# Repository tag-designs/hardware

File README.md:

# Tag Designs: Hardware

Board and mechanical designs for the ultralight archival data loggers (tags)
documented at <https://tag-designs.github.io/>.

| Path | Holds |
| --- | --- |
| `BoardDesigns/` | KiCad schematics and layouts for the tags and base boards, with their KiBot fabrication configurations |
| `Mechanical/` | OpenSCAD sources for cases, carriers and harness jigs |
| `docs/` | The hardware documentation site, published at <https://tag-designs.github.io/hardware/> |
| `STM32_open_pin_data` | ST's pin-data submodule, used by the design-rule helpers |

Board designs reach the shared symbol and footprint libraries through
`${KIPRJMOD}/../../`, so a board is tied to its depth in the directory tree.
Moving one between directories is more than a move.

## Regenerating the figures

The documentation's board renders and schematic PDFs are generated from the
KiCad files and committed, because the workflow that publishes the site has no
KiCad in it. After editing a board:

```sh
cmake -S BoardDesigns -B build-boards
cmake --build build-boards --target board-docs
```

[`BoardDesigns/REGENERATING.md`](BoardDesigns/REGENERATING.md) covers the
targets, the three checks that guard the figures, what each of their messages
means, and why generation is not done in CI. Read it before chasing a render
that looks wrong — in particular, `kicad-cli` reports nothing at all when it
cannot find a 3D model.

## License

Copyright &copy; 2018&ndash;2026 The Trustees of Indiana University.

This source describes Open Hardware and is licensed under the CERN Open
Hardware Licence Version 2 &mdash; Permissive (`CERN-OHL-P-2.0`). You may
redistribute and modify this source and make products using it under the terms
of that licence, whose full text is in [LICENSE](LICENSE) and at
<https://ohwr.org/cern_ohl_p_v2.txt>.

This source is distributed WITHOUT ANY EXPRESS OR IMPLIED WARRANTY, INCLUDING
OF MERCHANTABILITY, SATISFACTORY QUALITY AND FITNESS FOR A PARTICULAR PURPOSE.
Please see the licence for applicable conditions.

The `STM32_open_pin_data` submodule is ST's and carries its own license. The
software that runs on these boards lives in a separate repository under the MIT
License; see the
[project licensing summary](https://tag-designs.github.io/license/).

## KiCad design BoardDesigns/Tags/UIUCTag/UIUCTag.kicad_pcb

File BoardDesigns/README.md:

This directory contains the design files for the various PCBs and mechanical components.

Tools needed to build the boards

*   KiCad 10 (the boards are saved by KiCad 10; `kicad-cli` ships inside it)
*   Python 3 with Pillow, for trimming the renders
*   CMake 3.15 or later
*   KiBot, only if you want to run the fabrication configurations by hand

Tools needed to build base adapter plastic

*   openscad

Boards are grouped by role; each board is `<Group>/<board>/`:

* Tags/ -- the animal-borne tags themselves (BitTag, PresTag, CompassTag, IMUTag, ...);
  superseded tag variants are in Tags/Obsolete/
* Bases/ -- boards a tag plugs into: tagbase-* production baseboards and the MCU-carrying tag-breakout-* boards
* Prototypes/ -- tag circuits laid out as breakouts, ST eval daughter cards, imutag-daughtercard, UIUCBreakout
* Chargers/ -- MultiCharger and its JLCPCB variant
* Development/ -- bench and test equipment (TagPwrMonitor, js320-faceplate)

Shared infrastructure stays at this level: libraries/, kicad_libraries/,
kicad-helpers/, Kibot-config/, Templates/. Older retired boards live in Obsolete/.
Board files reach these through `${KIPRJMOD}/../../`, so moving a board to a
different depth means rebasing its lib tables, 3D-model paths, kibot include
and datasheets symlink.

## Generating schematic PDFs and board images

CMake generates two figures per documented board, both with `kicad-cli`:

| Figure | Written to | Drawn from |
| --- | --- | --- |
| Schematic PDF | `docs/src/schematics/<board>.pdf` | every `*.kicad_sch` in the board directory |
| 3D render, top | `docs/src/images/boards/<board>-top.png` | `<board>.kicad_pcb` |
| 3D render, bottom (tags only) | `docs/src/images/boards/<board>-bottom.png` | `<board>.kicad_pcb` |

They are written into the source tree and committed, because the site's
publishing workflow has no KiCad. Configure from the repository root:

```sh
cmake -S BoardDesigns -B build-boards
```

then build one of these targets:

| Target | Does |
| --- | --- |
| `board-docs` | PDFs and renders for every board whose sources changed |
| `board-schematics` | the schematic PDFs only |
| `board-renders` | the 3D renders only |
| `<board>-schematic` | one board's PDF, e.g. `CompassTag-schematic` |
| `<board>-renders` | one board's renders, e.g. `CompassTag-renders` |

```sh
cmake --build build-boards --target board-docs
cmake --build build-boards --target CompassTag-renders
```

None of them is part of the default build, so a plain `make` never rewrites
committed files. Only boards whose sources changed are redrawn; each render
takes about 45 seconds of raytracing, the PDFs almost nothing.

What the rules do:

* **PDF** — `kicad-cli sch export pdf --no-background-color`, so it prints on
  white whatever colour scheme the schematic is edited in. A hierarchical
  design exports every sheet into one file, and editing any sheet triggers a
  re-export.
* **Renders** — `kicad-cli pcb render --rotate 0,0,90 --zoom 0.5 --width 2400
  --height 2400 --quality high --preset follow_pcb_editor --background
  transparent`, then `kicad-helpers/fit_render.py` trims the image to the
  board and turns it portrait. Tags are drawn from both sides; bases and
  prototype carriers from the top only.
* **Stamps** — after each figure, the SHA-256 of its sources is written to
  `BoardDesigns/.render-stamps/` (`<board>.sha256`, `<board>.sch.sha256`), so
  `kicad-helpers/check_renders.py` can tell a stale figure without KiCad.

Configure prints the settings in force — check it:

```
-- kicad-cli: /Applications/KiCad/KiCad.app/Contents/MacOS/kicad-cli
-- Board renders: zoom 0.5, frame 2400 square, preset follow_pcb_editor
```

Override for an experiment with `-DRENDER_ZOOM=`, `-DRENDER_FRAME=` or
`-DRENDER_PRESET=`; if `kicad-cli` or Pillow is not found, point at them with
`-Dkicad_cli_EXECUTABLE=` or `-DPython3_EXECUTABLE=`.

Before regenerating, run `python3 BoardDesigns/kicad-helpers/check_models.py` —
`kicad-cli` silently draws a missing 3D model as nothing.

### Adding a board

Give the board directory a one-line `CMakeLists.txt` naming the `.kicad_pcb` /
`.kicad_sch` basename:

```cmake
add_board_renders(CompassTag)          # tags: top and bottom
add_board_renders_top(tagbase-v7)      # bases and prototypes: top only
```

and list it with `add_subdirectory(<Group>/<board>)` in
`BoardDesigns/CMakeLists.txt`. Boards not listed there get no targets.

### Fabrication outputs

Gerbers, BOM and CPL are no longer generated by CMake (the old
`<board>-pcb` targets are gone). Export them from KiCad's fabrication plugins,
or run the KiBot configurations in `Kibot-config/` by hand.

[`REGENERATING.md`](REGENERATING.md) has the full story: the checks that guard
the figures, what each of their messages means, and why the framing is set the
way it is.

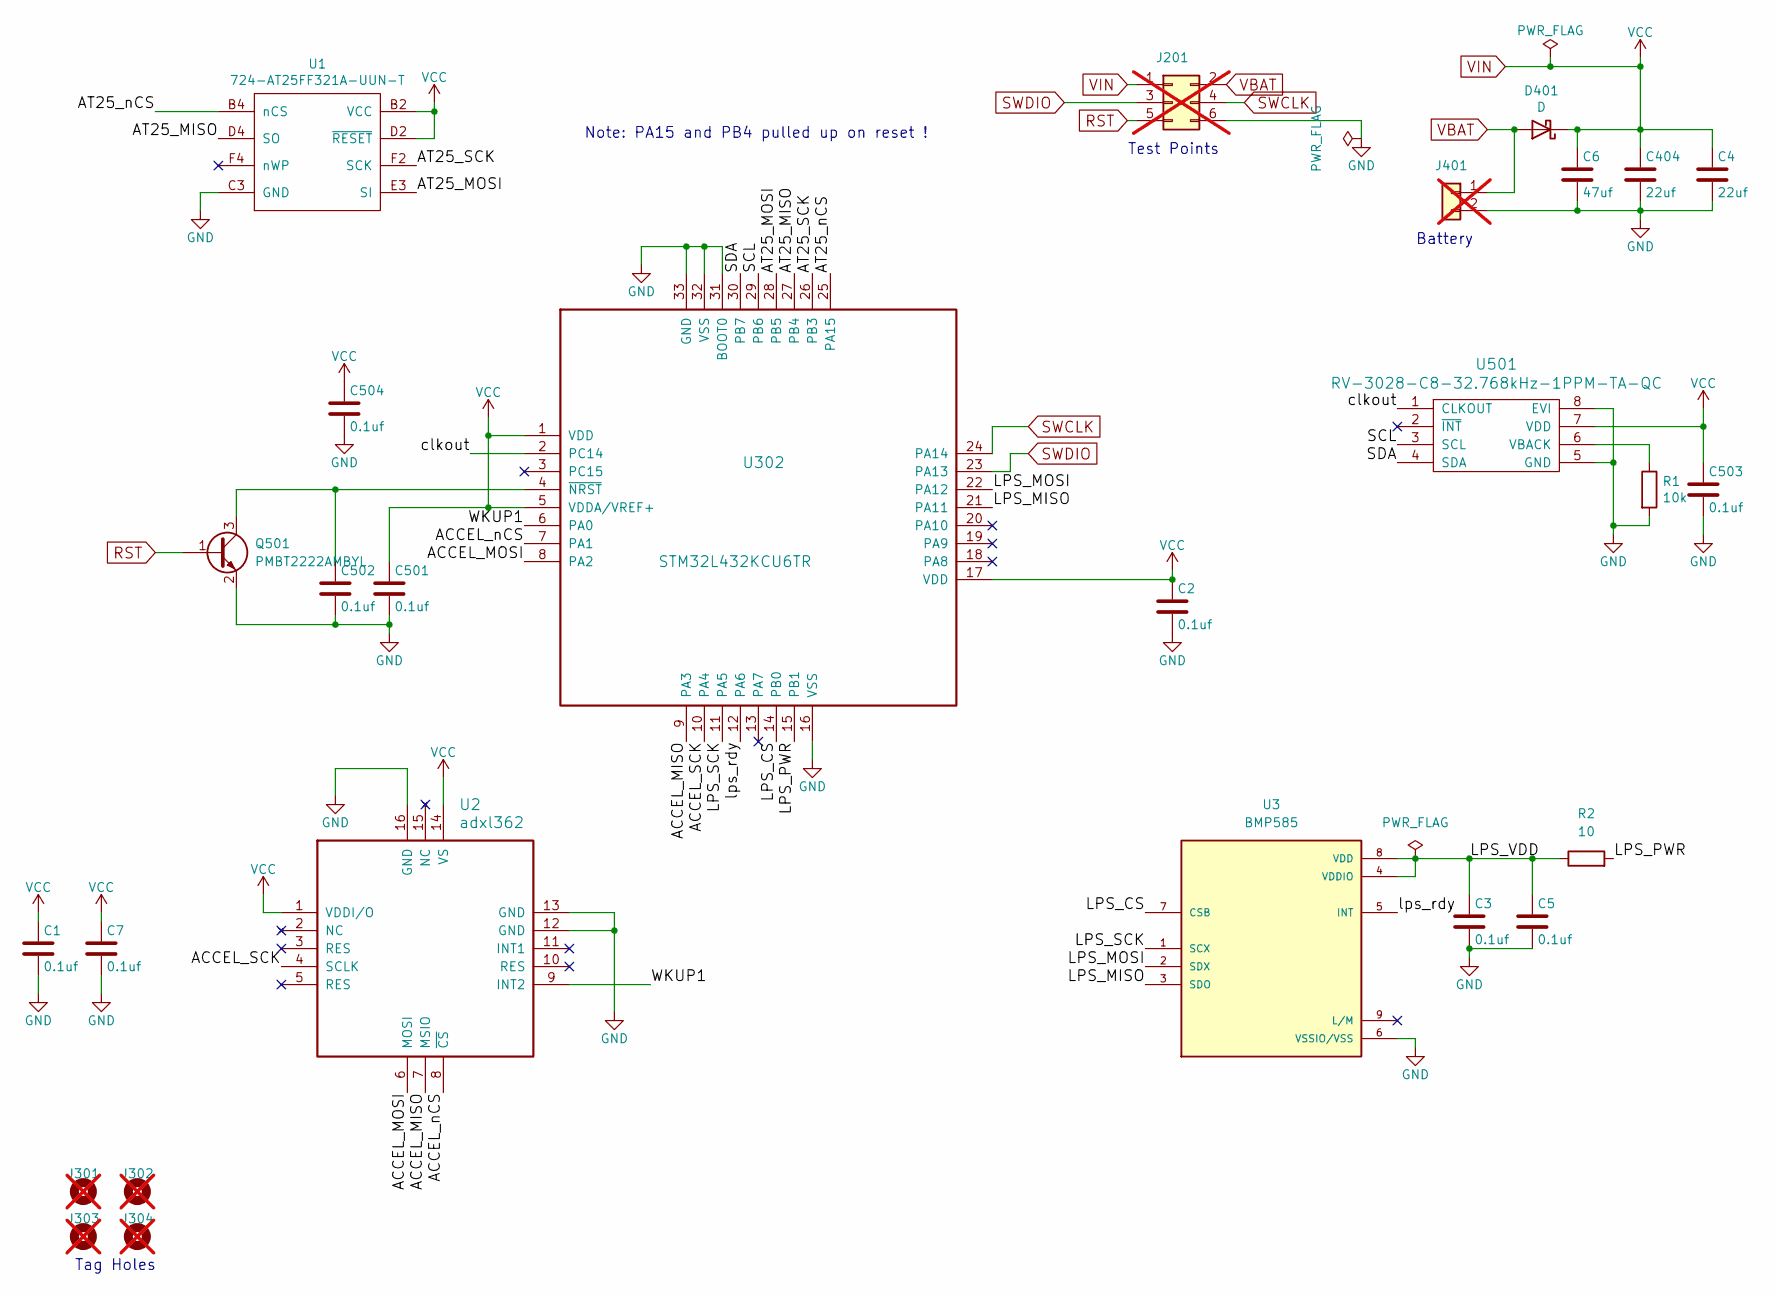
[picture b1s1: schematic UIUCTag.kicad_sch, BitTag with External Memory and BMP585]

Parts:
C1, C2, C3, C5, C7, C501, C502, C503, C504: 0.1uf; C_0201_0603Metric; MPN GRM033R61A104ME15D; LCSC C408130
C4, C404: 22uf; C_0402_1005Metric; MPN 04026D226MAT2A; LCSC C2179118
C6: 47uf; C_0603_1608Metric; MPN 06036D476MAT2A; LCSC C2185054
D401: D; D_0402_1005Metric; MPN CDBQC0130L-HF; LCSC C2886012
J201: CONN_02X04; tagpoints6; not fitted
J301, J302, J303, J304: Conn_01x01; taghole1.1mm; not fitted
J401: CONN_01X02; MS621; not fitted
Q501: PMBT2222AMBYL; SOT-883; MPN PMBT2222AMBYL; LCSC C552701
R1: 10k; R_0201_0603Metric; MPN RC0201FR-0710KL; LCSC C106225
R2: 10; R_0201_0603Metric; MPN RC0201FR-0710RL; LCSC C106226
U1: 724-AT25FF321A-UUN-T; adesto_wlcsp12; MPN AT25FF321A-UUN-T; LCSC C1858339
U2: adxl362; ADXL362; MPN ADXL362BCCZ-RL; LCSC C59641
U3: BMP585; LGA9_BMP585_BOS; PARTREV 1.2; LCSC C18184976
U302: STM32L432KCU6TR; QFN-32-1EP_5x5mm_P0.5mm_EP3.45x3.45mm; MPN STM32L432KCU6TR; LCSC C1337280
U501: RV-3028-C8-32.768kHz-1PPM-TA-QC; RV-3028-C8; MPN RV-3028-C8-32.768kHz-1PPM-TA-QC

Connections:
/ACCEL_MISO: U2.7 (MSIO), U302.9 (PA3)
/ACCEL_MOSI: U2.6 (MOSI), U302.8 (PA2)
/ACCEL_SCK: U2.4 (SCLK), U302.10 (PA4)
/ACCEL_nCS: U2.8 (~CS), U302.7 (PA1)
/AT25_MISO: U1.D4 (SO), U302.27 (PB4)
/AT25_MOSI: U1.E3 (SI), U302.28 (PB5)
/AT25_SCK: U1.F2 (SCK), U302.26 (PB3)
/AT25_nCS: U1.B4 (nCS), U302.25 (PA15)
/LPS_CS: U3.7 (CSB), U302.14 (PB0)
/LPS_MISO: U3.3 (SDO), U302.21 (PA11)
/LPS_MOSI: U3.2 (SDX), U302.22 (PA12)
/LPS_PWR: R2.2, U302.15 (PB1)
/LPS_SCK: U3.1 (SCX), U302.11 (PA5)
/LPS_VDD: C3.1, C5.1, R2.1, U3.4 (VDDIO), U3.8 (VDD)
/SCL: U302.29 (PB6), U501.3 (SCL)
/SDA: U302.30 (PB7), U501.4 (SDA)
/WKUP1: U2.9 (INT2), U302.6 (PA0)
/clkout: U302.2 (PC14), U501.1 (CLKOUT)
/lps_rdy: U3.5 (INT), U302.12 (PA6)
GND: C1.2, C2.2, C3.2, C4.2, C5.2, C6.2, C7.2, C404.2, C501.2, C502.2, C503.2, C504.2, J201.6, J401.2, Q501.2 (E), R1.2, U1.C3 (GND), U2.12 (GND), U2.13 (GND), U2.16 (GND), U3.6 (VSSIO/VSS), U302.16 (VSS), U302.31 (BOOT0), U302.32 (VSS), U302.33 (GND), U501.5 (GND), U501.8 (EVI)
unnamed: C502.1, Q501.3 (C), U302.4 (~NRST)
unnamed: R1.1, U501.6 (VBACK)
RST: J201.5, Q501.1 (B)
SWCLK: J201.4, U302.24 (PA14)
SWDIO: J201.3, U302.23 (PA13)
VBAT: D401.2 (A), J201.2, J401.1
VIN: C1.1, C2.1, C4.1, C6.1, C7.1, C404.1, C501.1, C503.1, C504.1, D401.1 (K), J201.1, U1.B2 (VCC), U1.D2 (~RESET), U2.1 (VDDI/O), U2.14 (VS), U302.1 (VDD), U302.5 (VDDA/VREF+), U302.17 (VDD), U501.7 (VDD)

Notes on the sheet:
Note: PA15 and PB4 pulled up on reset !
Tag Holes
Test Points
Battery

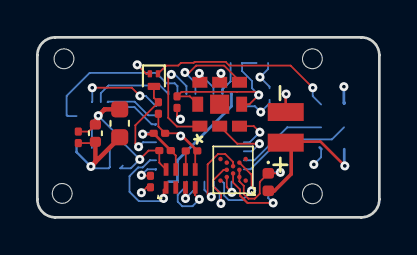
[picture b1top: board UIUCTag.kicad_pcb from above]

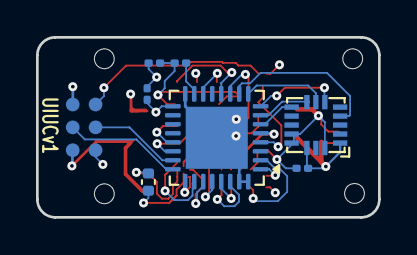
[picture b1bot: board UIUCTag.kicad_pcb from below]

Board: 4 copper layers, 19.0 x 10.0 mm, 27 parts (8 on the bottom side), 27 nets.

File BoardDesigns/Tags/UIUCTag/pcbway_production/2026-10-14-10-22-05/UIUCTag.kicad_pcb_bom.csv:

Designator,Quantity,Value,Footprint,Package,MPN,DNP,Mount_Type,KiLib_Generator,MFN,Field8,LCSC,DISTPN,Field9,Macrofab,Description,MAXIMUM_PACKAGE_HEIGHT,CREATOR,STANDARD,PARTREV,UNIT,MANUFACTURER
"C1, C2, C3, C5, C501, C502, C503, C504, C7",9,0.1uf,C_0201_0603Metric,,GRM033R61A104ME15D,,smt,"[C504,C7]SMD_2terminal_chip_molded; [C2]murata; [C501,C502,C503]Murata",Murata,${REFERENCE},C408130,"[C2]490-7229-2-ND; [C3,C5,C501,C502,C503,C504]490-10403-1-ND",${REFERENCE},MF-CAP-0402-0.1uF,,,,,,,
"C4, C404",2,22uf,C_0402_1005Metric,,04026D226MAT2A,,smt,04026D226MAT2A,AVX,${REFERENCE},C2179118,478-9839-1-ND,,,,,,,,,
C6,1,47uf,C_0603_1608Metric,,06036D476MAT2A,,smt,SMD_2terminal_chip_molded,KYOCERA AVX,,C2185054,478-11180-1-ND,,,,,,,,,
D401,1,D,D_0402_1005Metric,,CDBQC0130L-HF,,smt,CDBQC0130L-HF,COMCHIP,${REFERENCE},C2886012,641-1519-1-ND,,,,,,,,,
Q501,1,PMBT2222AMBYL,SOT-883,,PMBT2222AMBYL,,smt,,Nexperia,${REFERENCE},C552701,1727-2632-1-ND,,,,,,,,,
R1,1,10k,R_0201_0603Metric,,RC0201FR-0710KL,,smt,Yaego,Yaego,,C106225,311-10.0KMCT-ND,${REFERENCE},MF-RES-0402-10K,,,,,,,
R2,1,10,R_0201_0603Metric,,RC0201FR-0710RL,,smt,,Yageo,,C106226,,,,Resistor,,,,,,
U1,1,724-AT25FF321A-UUN-T,adesto_wlcsp12,,AT25FF321A-UUN-T,,smt,,adesto,${REFERENCE},C1858339,724-AT25FF321A-UUN-T,,,,,,,,,
U2,1,adxl362,ADXL362,,ADXL362BCCZ-RL,,smt,,Analog Devices,,C59641,,,,,,,,,,
U3,1,BMP585,LGA9_BMP585_BOS,,BMP585,,smt,,Bosch,,C18184976,,,,,1.96mm,NEZY,Manufacturer Recommendations,1.2,mm,Bosch
U302,1,STM32L432KCU6TR,QFN-32-1EP_5x5mm_P0.5mm_EP3.45x3.45mm,,STM32L432KCU6TR,,smt,STMicroelectronics,STMicroelectronics,${REFERENCE},C1337280,497-STM32L432KCU6TR-ND,,,,,,,,,
U501,1,RV-3028-C8-32.768kHz-1PPM-TA-QC,RV-3028-C8,,RV-3028-C8-32.768kHz-1PPM-TA-QC,,smt,,Micro Crystal,,C46471039,,,,,,,,,,

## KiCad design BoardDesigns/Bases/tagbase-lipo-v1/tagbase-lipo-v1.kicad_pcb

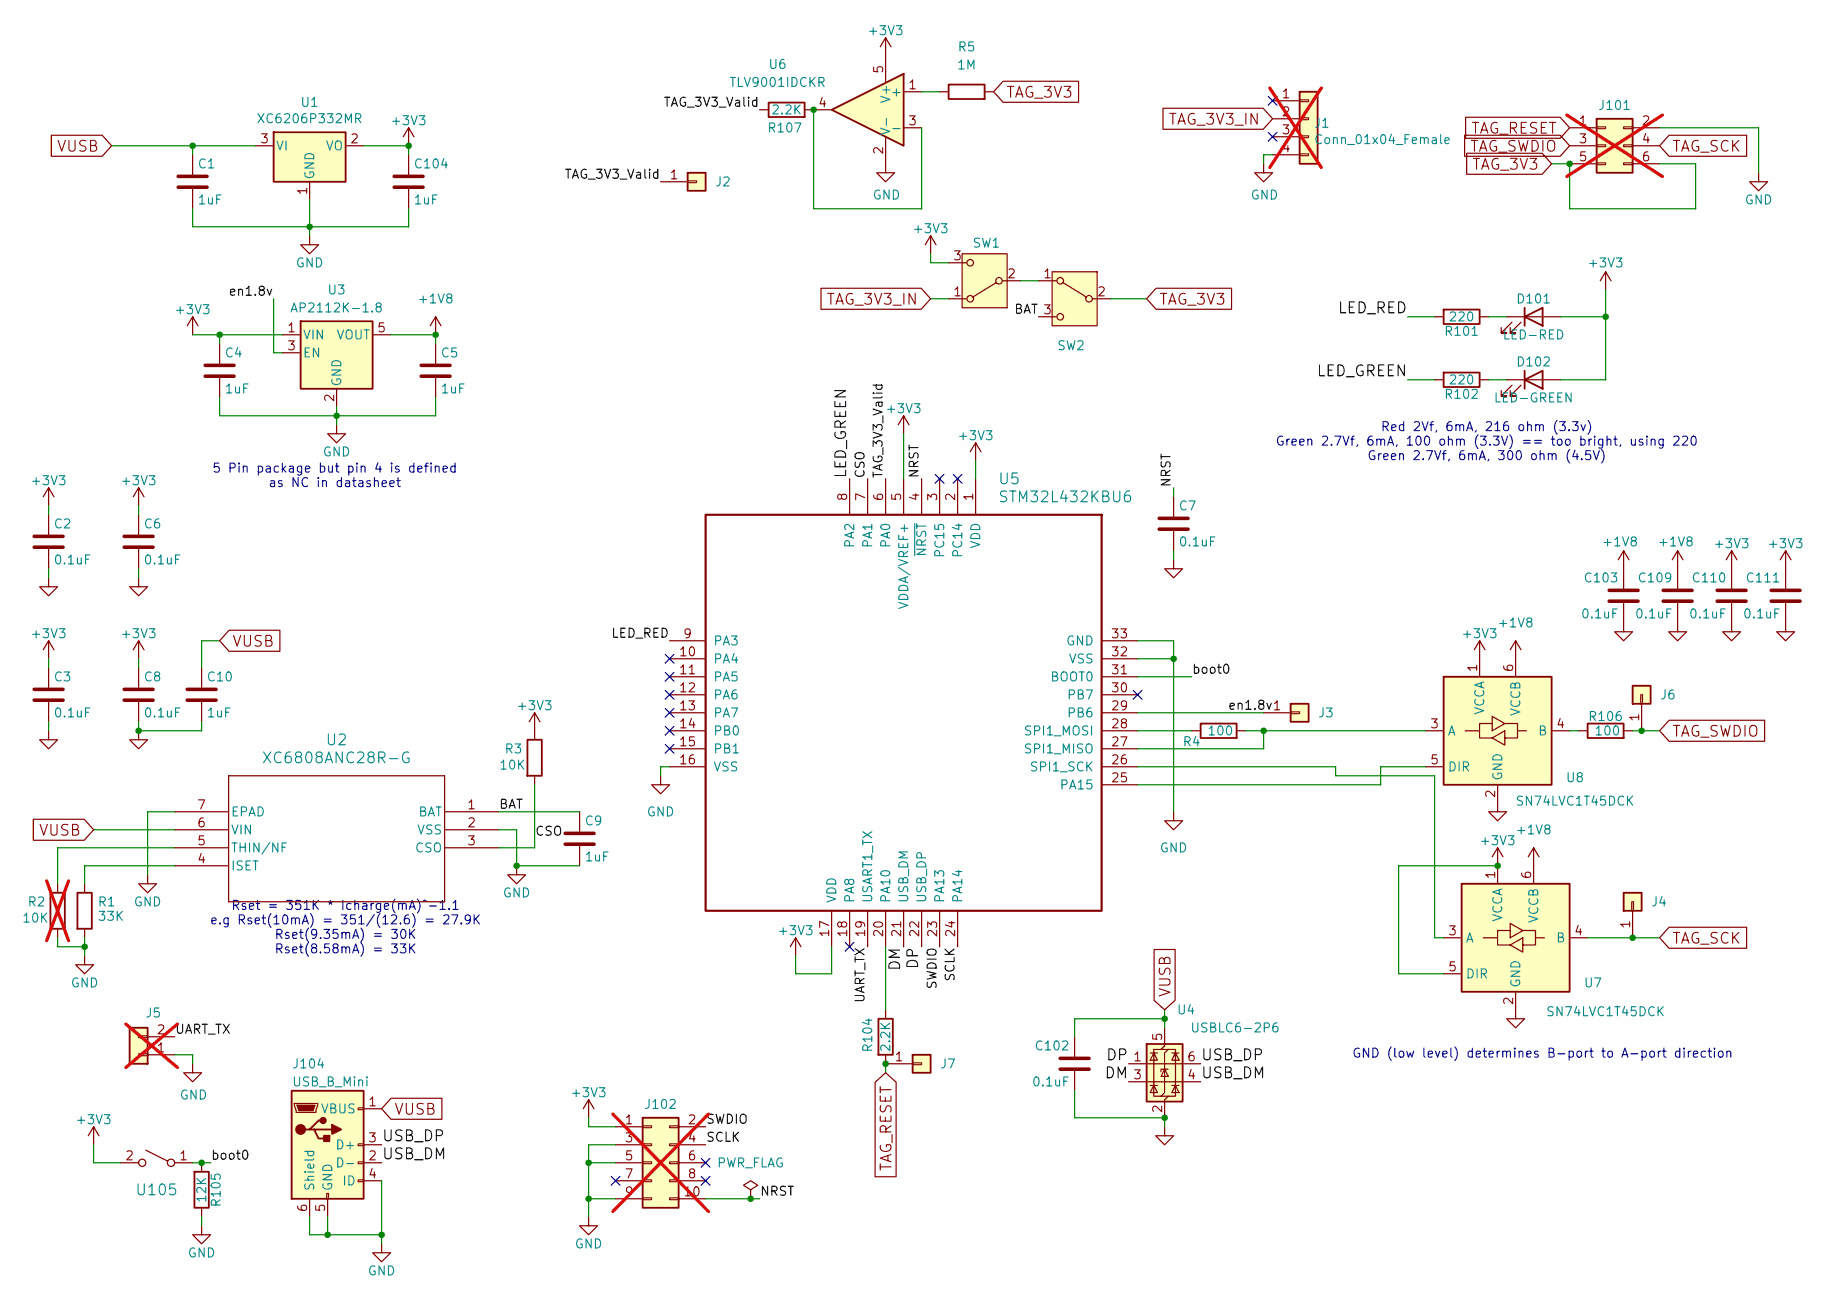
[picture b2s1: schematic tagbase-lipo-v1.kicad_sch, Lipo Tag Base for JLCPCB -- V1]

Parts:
C1, C4, C5, C9, C10, C104: 1uF; C_0402_1005Metric; MPN CL05A105KA5NQNC; LCSC C52923
C2, C3, C6, C7, C8, C102, C103, C109, C110, C111: 0.1uF; C_0402_1005Metric; MPN CL05B104KO5NNNC; LCSC C1525
D101: LED-RED; D_0805_2012Metric; MPN NCD0805R1; LCSC C84256
D102: LED-GREEN; D_0805_2012Metric; MPN KT-0805G; LCSC C2297
J1: Conn_01x04_Female; JST_XH_B04B-XH-AM_1x04_P2.50mm_Vertical; not fitted
J2, J3, J4, J6, J7: Conn_01x01; TestPoint_Pad_D1.5mm
J5: Conn_01x02; PinHeader_1x02_P2.54mm_Vertical; not fitted
J101: Conn_02x03_Odd_Even; 6pin_tagpoints_double_screws; not fitted
J102: Conn_02x05_Odd_Even; FTSH-105-01-F-D-K; not fitted
J104: USB_B_Mini; USB_Mini-B; MPN MINI 5PTP; LCSC C2681563
R1: 33K; R_0402_1005Metric; MPN 0402WGF3302TCE; LCSC C25779
R2: 10K; R_0402_1005Metric; MPN 0402WGF1002TCE; LCSC C25744; not fitted
R3: 10K; R_0402_1005Metric; MPN 0402WGF1002TCE; LCSC C25744
R4, R106: 100; R_0402_1005Metric; MPN 0402WGF1000TCE; LCSC C25076
R5: 1M; R_0402_1005Metric; MPN 0402WGF1004TCE; LCSC C26083
R101, R102: 220; R_0603_1608Metric; MPN 0603WAF1000T5E; LCSC C22775
R104, R107: 2.2K; R_0402_1005Metric; MPN 0402WGF2201TCE; LCSC C25879
R105: 12K; R_0402_1005Metric; MPN 0402WGF1202TCE; LCSC C25752
SW1, SW2: SW_SPDT; CJS-1200B_NDC; MPN CJS-1200B2; LCSC C35817163
U1: XC6206P332MR; SOT-23-3; MPN XC6206P332MR; LCSC C5446
U2: XC6808ANC28R-G; xc6808; MPN XC6808ANC28R-G; LCSC C7123934
U3: AP2112K-1.8; SOT-23-5; MPN AP2112K-1.8TRG1(MS); LCSC C22365428
U4: USBLC6-2P6; SOT-666; MPN USBLC6-2P6; LCSC C2827693
U5: STM32L432KBU6; UFQFPN-32-1EP_5x5mm_P0.5mm_EP3.5x3.5mm; MPN STM32L432KBU6; LCSC C94784
U6: TLV9001IDCKR; SOT-353_SC-70-5; MPN TLV9001IDCKR; LCSC C398362
U7, U8: SN74LVC1T45DCK; SOT-363_SC-70-6; MPN SN74LVC1T45DCKR; LCSC C9382
U105: Tactile Switch; SW_SPST_TS_1187; MPN TS-1187A-C-E-B; LCSC C318889

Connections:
+1V8: C5.1, C103.1, C109.1, U3.5 (VOUT), U7.6 (VCCB), U8.6 (VCCB)
+3V3: C2.1, C3.1, C4.1, C6.1, C8.1, C104.1, C110.1, C111.1, D101.2 (A), D102.2 (A), J102.1, R3.1, SW1.3 (C), U1.2 (VO), U3.1 (VIN), U5.1 (VDD), U5.5 (VDDA/VREF+), U5.17 (VDD), U6.5 (V+), U7.1 (VCCA), U7.5 (DIR), U8.1 (VCCA), U105.2 (B)
/BAT: C9.1, SW2.3 (C), U2.1 (BAT)
/CSO: R3.2, U2.3 (CSO), U5.7 (PA1)
/DM: U4.3 (I/O2), U5.21 (USB_DM)
/DP: U4.1 (I/O1), U5.22 (USB_DP)
/LED_GREEN: R102.2, U5.8 (PA2)
/LED_RED: R101.2, U5.9 (PA3)
/NRST: C7.1, J102.10, U5.4 (~NRST)
/SCLK: J102.4, U5.24 (PA14)
/SWDIO: J102.2, U5.23 (PA13)
/TAG_3V3_Valid: J2.1 (Pin_1_1), R107.1, U5.6 (PA0)
/UART_TX: J5.2, U5.19 (USART1_TX)
/USB_DM: J104.2 (D-), U4.4 (I/O2)
/USB_DP: J104.3 (D+), U4.6 (I/O1)
/boot0: R105.2, U5.31 (BOOT0), U105.1 (A)
/en1.8v: J3.1 (Pin_1_1), U3.3 (EN), U5.29 (PB6)
GND: C1.2, C2.2, C3.2, C4.2, C5.2, C6.2, C7.2, C8.2, C9.2, C10.2, C102.2, C103.2, C104.2, C109.2, C110.2, C111.2, J1.4, J5.1, J101.2, J102.3, J102.5, J102.9, J104.4 (ID), J104.5 (GND), J104.6 (Shield), R1.2, R2.2, R105.1, U1.1 (GND), U2.2 (VSS), U2.7 (EPAD), U3.2 (GND), U4.2 (GND), U5.16 (VSS), U5.32 (VSS), U5.33 (GND), U6.2 (V-), U7.2 (GND), U8.2 (GND)
unnamed: D101.1 (K), R101.1
unnamed: D102.1 (K), R102.1
unnamed: SW1.2 (B), SW2.1 (A)
unnamed: R1.1, U2.4 (ISET)
unnamed: R2.1, U2.5 (THIN/NF)
unnamed: R104.1, U5.20 (PA10)
unnamed: U5.25 (PA15), U8.5 (DIR)
unnamed: U5.26 (SPI1_SCK), U7.3 (A)
unnamed: R4.2, U5.27 (SPI1_MISO), U8.3 (A)
unnamed: R4.1, U5.28 (SPI1_MOSI)
unnamed: R5.1, U6.1 (+)
unnamed: R107.2, U6.3 (-), U6.4
unnamed: R106.1, U8.4 (B)
TAG_3V3: J101.5, J101.6, R5.2, SW2.2 (B)
TAG_3V3_IN: J1.2, SW1.1 (A)
TAG_RESET: J7.1 (Pin_1_1), J101.1, R104.2
TAG_SCK: J4.1 (Pin_1_1), J101.4, U7.4 (B)
TAG_SWDIO: J6.1 (Pin_1_1), J101.3, R106.2
VUSB: C1.1, C10.1, C102.1, J104.1 (VBUS), U1.3 (VI), U2.6 (VIN), U4.5 (VBUS)

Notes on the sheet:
Rset = 351K * Icharge(mA)^-1.1 e.g Rset(10mA) = 351/(12.6) = 27.9K Rset(9.35mA) = 30K Rset(8.58mA) = 33K
5 Pin package but pin 4 is defined as NC in datasheet
GND (low level) determines B-port to A-port direction
Red 2Vf, 6mA, 216 ohm (3.3v) Green 2.7Vf, 6mA, 100 ohm (3.3V) == too bright, using 220 Green 2.7Vf, 6mA, 300 ohm (4.5V)

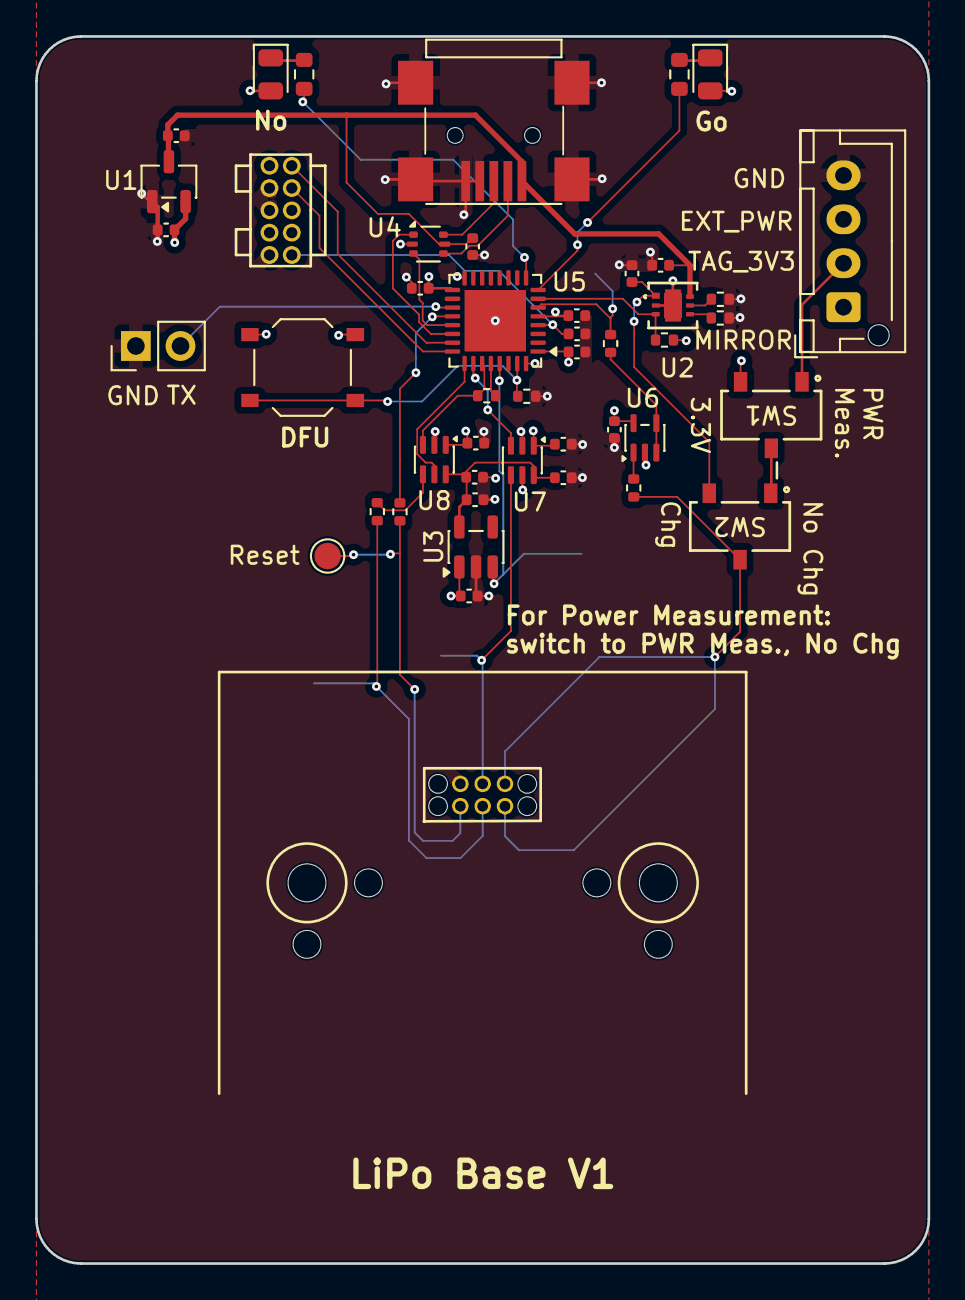
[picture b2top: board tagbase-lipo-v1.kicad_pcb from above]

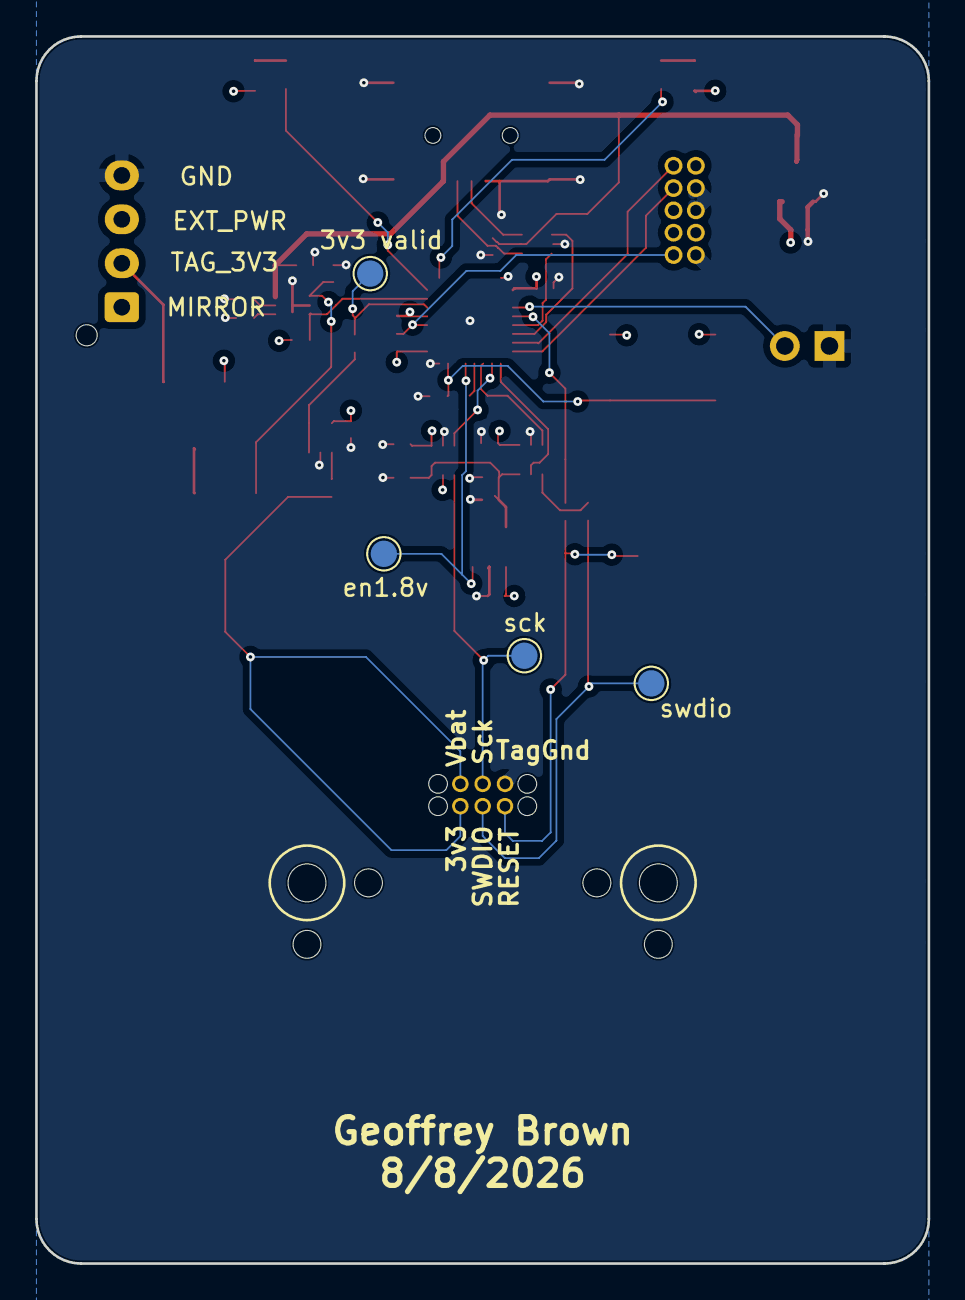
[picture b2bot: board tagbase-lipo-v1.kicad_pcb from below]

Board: 4 copper layers, 50.8 x 69.9 mm, 50 parts (4 on the bottom side), 37 nets.

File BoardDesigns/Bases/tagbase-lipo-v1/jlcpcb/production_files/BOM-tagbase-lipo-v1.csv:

Comment,Designator,Footprint,LCSC,Quantity
0.1uF,"C102,C103,C109,C110,C111,C2,C3,C6,C7,C8",C_0402_1005Metric,C1525,10
100,"R106,R4",R_0402_1005Metric,C25076,2
10K,R3,R_0402_1005Metric,C25744,1
12K,R105,R_0402_1005Metric,C25752,1
1M,R5,R_0402_1005Metric,C26083,1
1uF,"C1,C10,C104,C4,C5,C9",C_0402_1005Metric,C52923,6
2.2K,"R104,R107",R_0402_1005Metric,C25879,2
220,"R101,R102",R_0603_1608Metric,C22775,2
33K,R1,R_0402_1005Metric,C25779,1
AP2112K-1.8,U3,SOT-23-5,C22365428,1
LED-GREEN,D102,D_0805_2012Metric,C2297,1
LED-RED,D101,D_0805_2012Metric,C84256,1
SN74LVC1T45DCK,"U7,U8",SOT-363_SC-70-6,C9382,2
STM32L432KBU6,U5,UFQFPN-32-1EP_5x5mm_P0.5mm_EP3.5x3.5mm,C94784,1
SW_SPDT,"SW1,SW2",CJS-1200B_NDC,C35817163,2
TLV9001IDCKR,U6,SOT-353_SC-70-5,C398362,1
Tactile Switch,U105,SW_SPST_TS_1187,C318889,1
USBLC6-2P6,U4,SOT-666,C2827693,1
USB_B_Mini,J104,USB_Mini-B,C2681563,1
XC6206P332MR,U1,SOT-23-3,C5446,1
XC6808ANC28R-G,U2,xc6808,C7123934,1

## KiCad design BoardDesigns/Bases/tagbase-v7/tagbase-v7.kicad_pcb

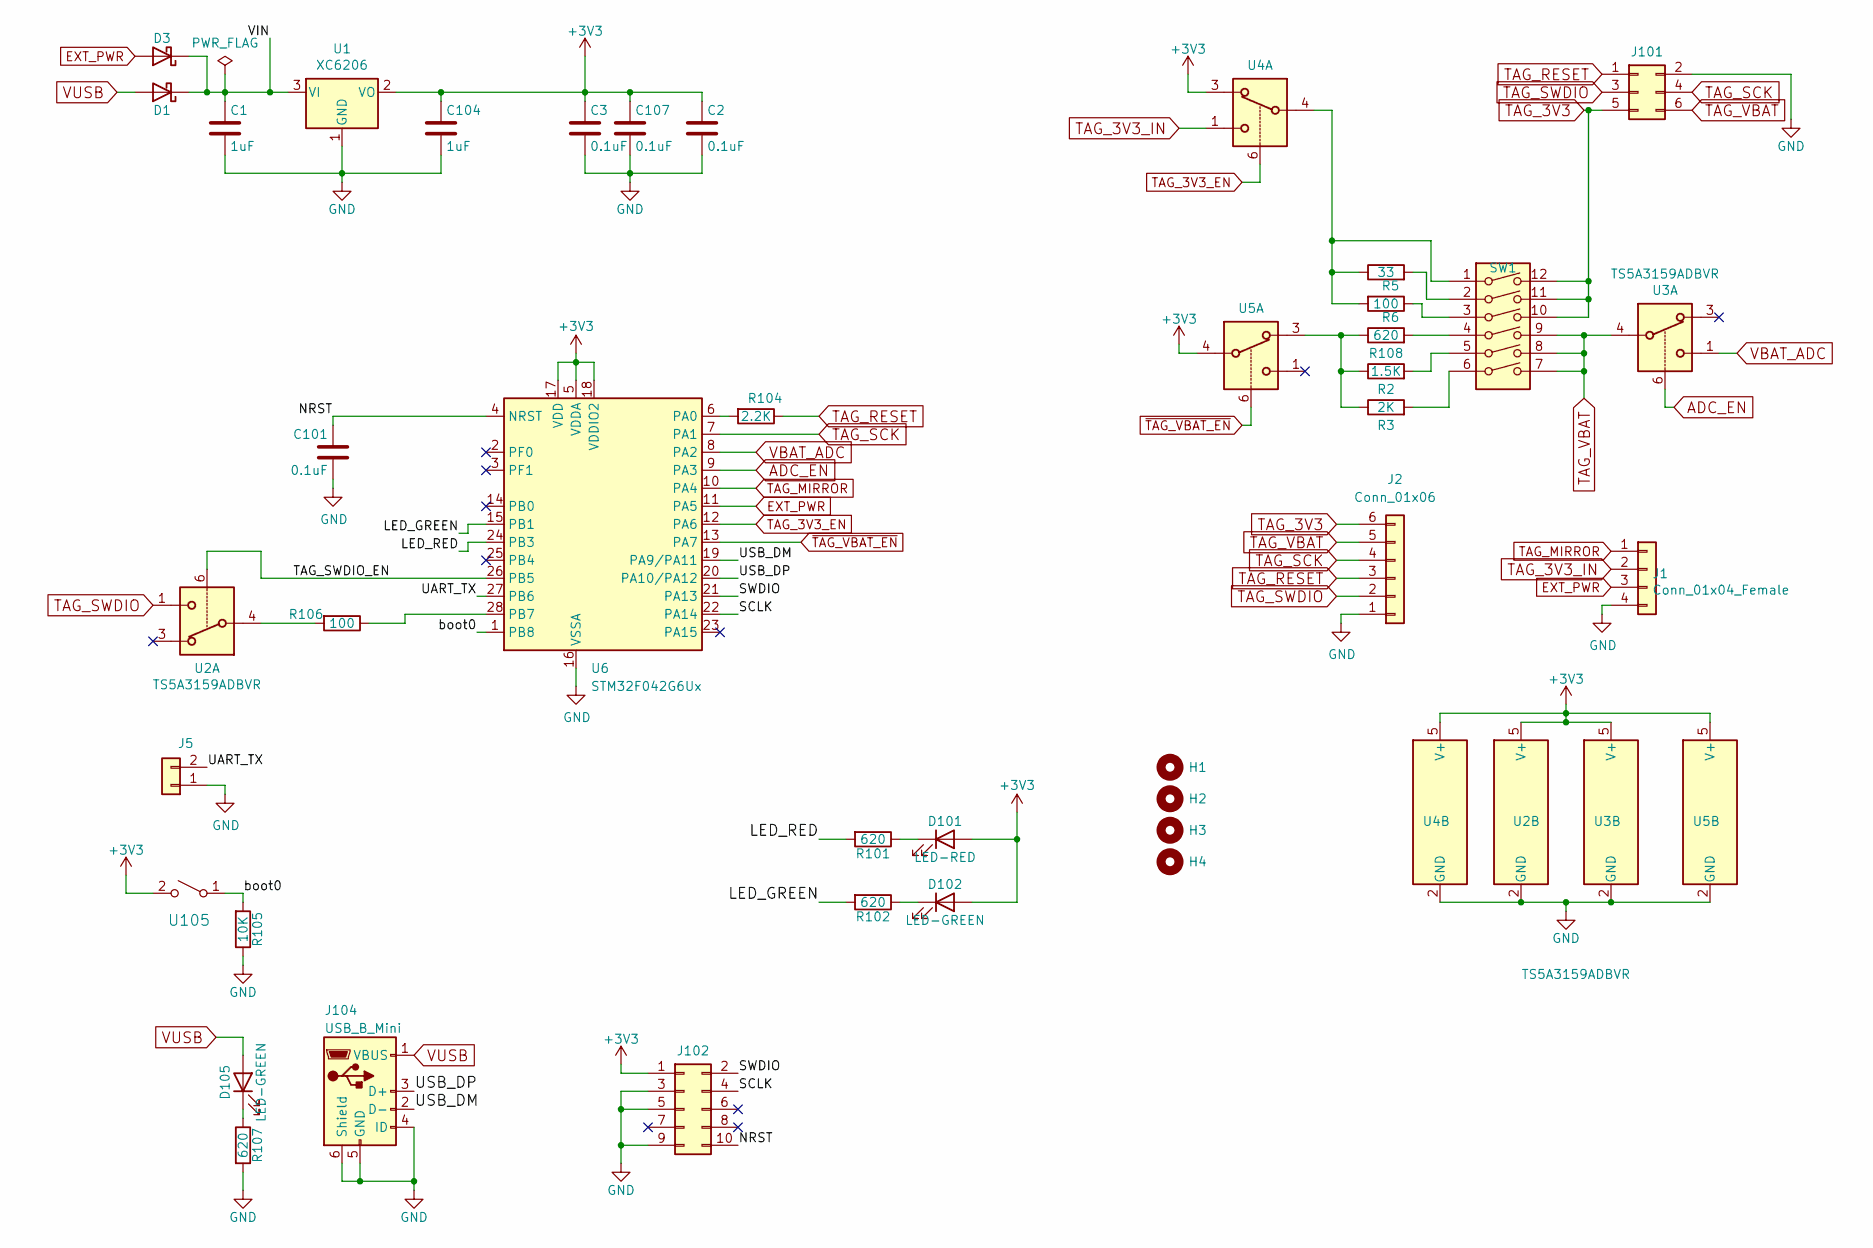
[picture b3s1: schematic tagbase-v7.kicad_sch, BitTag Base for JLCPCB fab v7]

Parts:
C1, C104: 1uF; C_0603_1608Metric; MPN CL10A105KB8NNNC; LCSC C15849
C2, C3, C101, C107: 0.1uF; C_0603_1608Metric; MPN CC0603KRX7R9BB104; LCSC C14663
D1, D3: DIODE; D_SOD-123; MPN B5819W; LCSC C8598
D101: LED-RED; LED_0603_1608Metric; MPN KT-0603R; LCSC C2286
D102, D105: LED-GREEN; LED_0603_1608Metric; MPN 19-217/GHC-YR1S2/3T; LCSC C72043
H1, H2, H3, H4: MountingHole; MountingHole_2.5mm
J1: Conn_01x04_Female; JST_XH_B04B-XH-AM_1x04_P2.50mm_Vertical
J2: Conn_01x06; JST_B6B-ZR(LF)(SN)
J5: Conn_01x02; PinHeader_1x02_P2.54mm_Vertical
J101: Conn_02x03_Odd_Even; 6pin_tagpoints_new_offset
J102: Conn_02x05_Odd_Even; FTSH-105-01-F-D-K
J104: USB_B_Mini; USB_Mini-B; MPN MINI 5PTP; LCSC C2681563
R2: 1.5K; R_0603_1608Metric; MPN 0603WAF1501T5E; LCSC C22843
R3: 2K; R_0603_1608Metric; MPN 0603WAF2001T5E; LCSC C22975
R5: 33; R_0603_1608Metric; MPN 0603WAF330JT5E; LCSC C23140
R6, R106: 100; R_0603_1608Metric; MPN 0603WAF1000T5E; LCSC C22775
R101, R102, R107, R108: 620; R_0603_1608Metric; MPN 0603WAF6200T5E; LCSC C23220
R104: 2.2K; R_0603_1608Metric; MPN 0603WAF1002T5E; LCSC C4190
R105: 10K; R_0603_1608Metric; MPN 0603WAF1002T5E; LCSC C25804
SW1: SW_DIP_x04; SW_DIP_SPSTx06_Slide_KingTek_DSHP06TS_W7.62mm_P1.27mm; MPN DSHP06TSGER; LCSC C3293146
U1: XC6206; SOT-23-3; MPN XC6206P332MR; LCSC C5446
U2, U3, U4, U5: TS5A3159ADBVR; SOT-23-6; MPN TS5A3159ADBVR; LCSC C128405
U6: STM32F042G6Ux; QFN-28_4x4mm_P0.5mm; MPN STM32F042G6U6; LCSC C961597
U105: Tactile Switch; SW_SPST_TS_1187; MPN TS-1187A-C-E-B; LCSC C318889

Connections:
+3V3: C2.1, C3.1, C104.1, C107.1, D101.2 (A), D102.2 (A), J102.1, U1.2 (VO), U2.5 (V+), U3.5 (V+), U4.3, U4.5 (V+), U5.4, U5.5 (V+), U6.5 (VDDA), U6.17 (VDD), U6.18 (VDDIO2), U105.2 (B)
/LED_GREEN: R102.2, U6.15 (PB1)
/LED_RED: R101.2, U6.24 (PB3)
/NRST: C101.1, J102.10, U6.4 (NRST)
/SCLK: J102.4, U6.22 (PA14)
/SWDIO: J102.2, U6.21 (PA13)
/TAG_SWDIO_EN: U2.6, U6.26 (PB5)
/UART_TX: J5.2, U6.27 (PB6)
/USB_DM: J104.2 (D-), U6.19 (PA9/PA11)
/USB_DP: J104.3 (D+), U6.20 (PA10/PA12)
/VIN: C1.1, D1.1 (K), D3.1 (K), U1.3 (VI)
/boot0: R105.2, U6.1 (PB8), U105.1 (A)
ADC_EN: U3.6, U6.9 (PA3)
EXT_PWR: D3.2 (A), J1.3, U6.11 (PA5)
GND: C1.2, C2.2, C3.2, C101.2, C104.2, C107.2, J1.4, J2.1, J5.1, J101.2, J102.3, J102.5, J102.9, J104.4 (ID), J104.5 (GND), J104.6 (Shield), R105.1, R107.2, U1.1 (GND), U2.2 (GND), U3.2 (GND), U4.2 (GND), U5.2 (GND), U6.16 (VSSA)
unnamed: D101.1 (K), R101.1
unnamed: D102.1 (K), R102.1
unnamed: D105.1 (K), R107.1
unnamed: R2.2, SW1.5
unnamed: R3.2, SW1.6
unnamed: R5.1, R6.2, SW1.1, U4.4
unnamed: R5.2, SW1.2
unnamed: R6.1, SW1.3
unnamed: R104.2, U6.6 (PA0)
unnamed: R106.1, U6.28 (PB7)
unnamed: R106.2, U2.4
unnamed: R2.1, R3.1, R108.1, U5.3
unnamed: R108.2, SW1.4
TAG_3V3: J2.6, J101.5, SW1.10, SW1.11, SW1.12
TAG_3V3_EN: U4.6, U6.12 (PA6)
TAG_3V3_IN: J1.2, U4.1
TAG_MIRROR: J1.1, U6.10 (PA4)
TAG_RESET: J2.3, J101.1, R104.1
TAG_SCK: J2.4, J101.4, U6.7 (PA1)
TAG_SWDIO: J2.2, J101.3, U2.1
TAG_VBAT: J2.5, J101.6, SW1.7, SW1.8, SW1.9, U3.4
VBAT_ADC: U3.1, U6.8 (PA2)
VUSB: D1.2 (A), D105.2 (A), J104.1 (VBUS)
~TAG_VBAT_EN: U5.6, U6.13 (PA7)

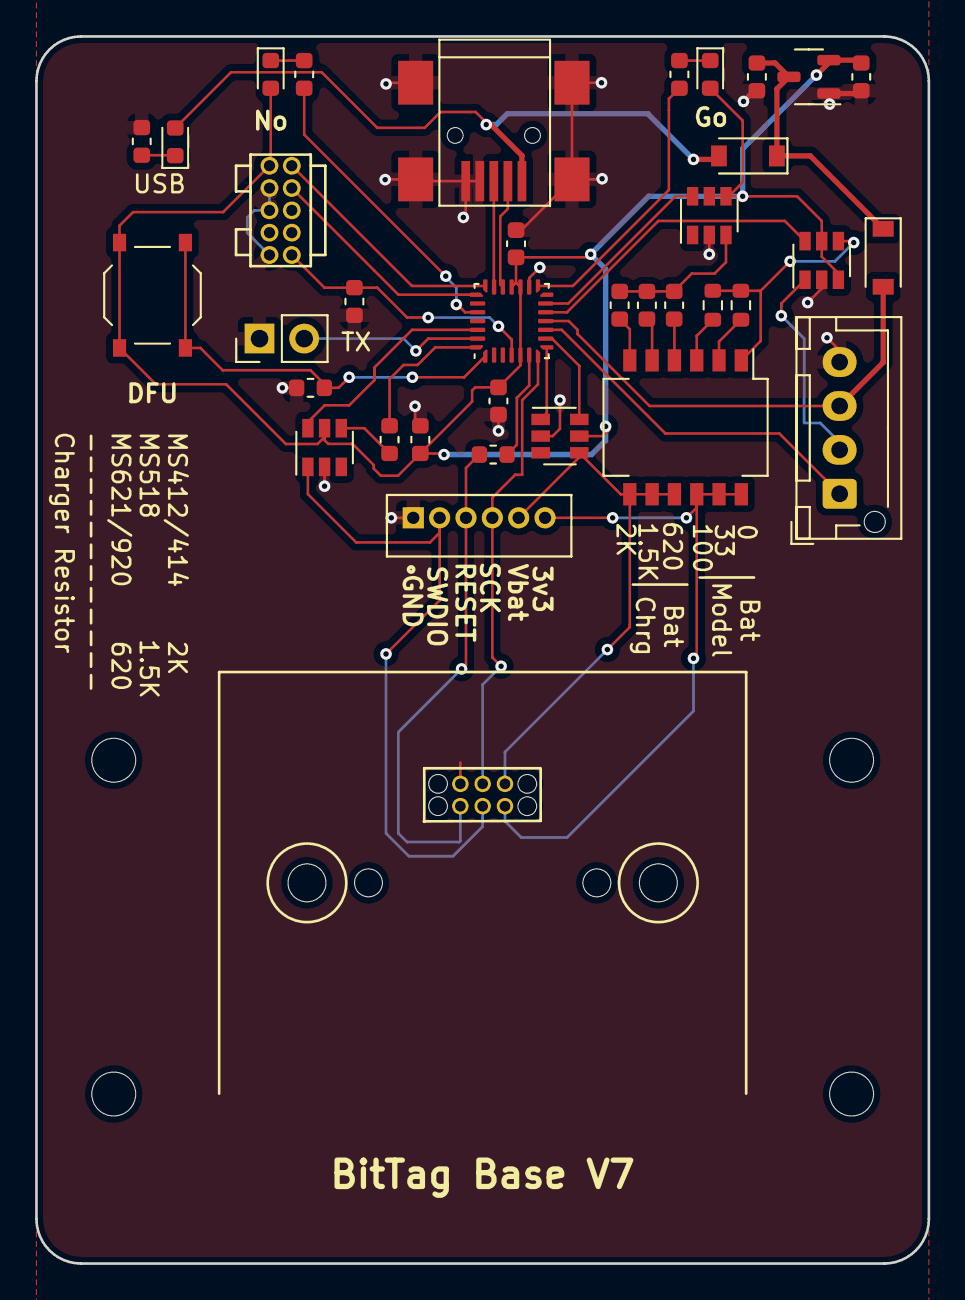
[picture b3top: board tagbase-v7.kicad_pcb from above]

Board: 2 copper layers, 50.8 x 69.9 mm, 40 parts (0 on the bottom side), 39 nets.

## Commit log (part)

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2022-08-15 fix build
2022-08-16 add submodules
2022-08-16 gitignore
2022-09-16 add licenses
2022-11-25 update PresTag components
2022-11-25 update prestag yaml file
2022-12-14 update prestag for manufacturing
2022-12-21 update Prestag
2023-02-02 update tagbase
2023-02-24 checkpoint
2023-03-16 revise prestag
2023-03-17 update prestag hardware
2023-03-17 checkpoint Prestagv4
2023-03-17 move prestag pcb origin
2023-03-17 added prestag
2023-03-17 update lps27 part number
2023-03-17 move origin for BitTagv7
2023-03-18 update kibot yaml for prestag
2023-03-19 developing mechanical for PresTag
2023-04-09 move main branch to qt6
2023-04-15 update BitTagvc plastic
2023-04-30 Board for spray coating tags
2023-05-03 fix adc
2023-05-13 added PresTagv5
2023-05-13 update cmake
2023-05-15 Change CMakeLists for building tags
2023-05-18 remove arm directive from CMake
2023-05-19 added BitTagNG pcb
2023-05-19 chibios 21 port working for PresTag, BitTagv6
2023-05-27 update tag base plastic
2023-05-31 add tagbase v7 for jlcpcb
2023-06-02 added tagbase v7
2023-06-02 update tagbase v7
2023-06-02 add tagbase v7 cmakefile
2023-06-02 renamed tagbase-v7
2023-06-02 update kibot yaml
2023-06-03 fix tagbase v7 for jlcpcb fabrication
2023-06-03 added jlcpcb multicharger
2023-06-04 complete JLCPCB multicharger
2023-06-05 archive 3d models
2023-06-06 convert multicharger for jlcpcb
2023-06-11 update clearances for bittag base
2023-06-13 update multicharger
2023-06-26 remove voltage shutdown from BitTag
2023-07-07 bittag-base-v7
2023-07-08 correct multicharger load resistor part numbers
2023-07-08 update multicharger to use basic parts
2023-07-09 added comments to multicharger
2023-07-09 updated jlcpcb multicharger
2023-07-10 added 3d models to BitTagNG
2023-07-12 update multicharger resistors
2023-07-13 reduce pcb board clearance on vc plastic
2023-07-13 update parts in BitTagNG
2023-07-16 update decoupling for adxl367
2023-07-16 update bittagng
2023-07-21 optimize BitTagNG pcb
2023-09-22 update BitTagNG for pcbway
2024-03-11 reduced via/track sizes for BitTagNG
2024-03-14 acceltagng proto software
2024-03-27 added capacitor to BitTagNG
2024-03-28 reduce pad width of adxl367 to 0.32mm from 0.33mm for pcbway
2024-04-15 started new breakout board
2024-04-23 revert BitTagNG footprint for adxl367
2024-05-03 Start BitTagv8
2025-01-13 changed delays for PresTag data
2025-01-30 update prestag hardware and software
2025-02-05 added bmp581 breakout code and board
2025-02-05 PresTagBMP581
2025-02-19 tweak design
2025-02-19 update design
2025-02-24 ignore .vscode directory
2025-02-24 seems to build on windows
2025-02-25 patch for os x
2025-02-26 building on M1 mac now
2025-02-28 Pruned inactive software/hardware. See branch archive2-28-25 for pruned files
2025-02-28 updated latest board design
2025-03-07 refactoring of qtmonitor complete
2025-03-13 fixed small issues with qtprogram
2025-03-16 adding prestag format
2025-03-24 working on compass board
2025-03-25 finish breakout board with mag, accel, pres
2025-04-16 designed compass tag
2025-04-23 added bit/pressure tag design
2025-04-25 checkpoint hardware designs
2025-06-04 checkpoint -- order compass proto board
2025-06-05 change drill file location
2025-06-05 update kibot files to generate drill file
2025-06-05 update proto boards
2025-06-06 update prototype boards
2025-06-18 Working board file for tag-breakout-base-l432-v1
2025-09-12 BitTag case design
2025-09-15 3d model of bittag case
2025-09-19 compass tag sensor calibration working
2025-11-02 tweak compasstag
2025-12-29 compass tag base
2026-01-05 tweek compass tag
2026-02-11 add imu tag
2026-02-13 complete IMU tag
2026-02-26 update compasstag hardware
2026-02-26 update parts
2026-03-02 update flash for imu tag
2026-03-03 added base test board
2026-03-03 added nucleoshield template
2026-03-04 imu breakout board
2026-03-11 restructure data logging
2026-03-15 imu tag breakout
2026-03-27 test of 4 layer imu board
2026-03-30 update hardware designs
2026-04-07 new steval breakout with nand flash
2026-04-27 CompassTag power usage corrected
2026-04-27 strip CMakeLists.txt
2026-05-01 update tagbase lipo design
2026-05-06 added torpor tag
2026-05-07 Torper tag breakout
2026-05-09 changed TorporTag to using local library
2026-05-09 removed large file
2026-05-09 updated libraries for TorporTagBreakout
2026-05-10 rearrange tag libraries
2026-05-11 big checking after adding codex skills
2026-05-12 Update CompassTag
2026-05-12 reorganize
2026-05-23 tag-breakout-l432v2 board
2026-05-23 update tag-breakout-l432v2
2026-06-08 new lipo breakout
2026-06-09 check in 2 layer board
2026-06-09 final layout tweaking of tag-breakout-l432-u375-lipo-v1
2026-06-12 Update IMU breakout and bittag base designs
2026-06-15 IMUBreakout and tag-breakout-l432-lipo-v1 submit for fab
2026-06-22 tag power monitor board

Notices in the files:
parts and their libraries:
Copyright 2016 Accelerated Designs. All rights reserved.
